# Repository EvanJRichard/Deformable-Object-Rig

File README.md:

Deformable-Object-Rig
=====================

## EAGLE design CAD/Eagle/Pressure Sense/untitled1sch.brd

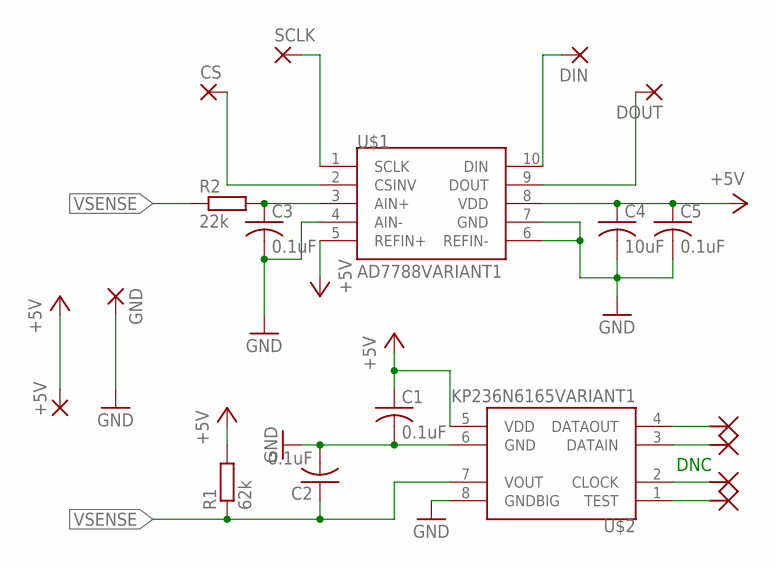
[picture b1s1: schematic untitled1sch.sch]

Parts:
+5V: WIREPAD1,6/0,8; 1,6/0,8
C1, C2, C3, C5: 0.1uF; C0805
C4: 10uF; C0805
CS: WIREPAD1,6/0,8; 1,6/0,8
DIN: WIREPAD1,6/0,8; 1,6/0,8
DOUT: WIREPAD1,6/0,8; 1,6/0,8
GND: WIREPAD1,6/0,8; 1,6/0,8
R1: 62k; R0603
R2: 22k; R0603
SCLK: WIREPAD1,6/0,8; 1,6/0,8
U$1: AD7788VARIANT1; AD7788
U$2: KP236N6165VARIANT1; KP236N6165

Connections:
+5V: +5V.1, C1.1, C4.1, C5.1, R1.2, U$1.5 (REFIN+), U$1.8 (VDD), U$2.5 (VDD)
GND: C1.2, C2.2, C3.2, C4.2, C5.2, GND.1, U$1.4 (AIN-), U$1.6 (REFIN-), U$1.7 (GND), U$2.6 (GND), U$2.8 (GNDBIG)
unnamed: CS.1, U$1.2 (CSINV)
unnamed: DIN.1, U$1.10 (DIN)
unnamed: DOUT.1, U$1.9 (DOUT)
RENAMED: C3.1, R2.2, U$1.3 (AIN+)
SCLK: SCLK.1, U$1.1 (SCLK)
VSENSE: C2.1, R1.1, R2.1, U$2.7 (VOUT)

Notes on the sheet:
DNC

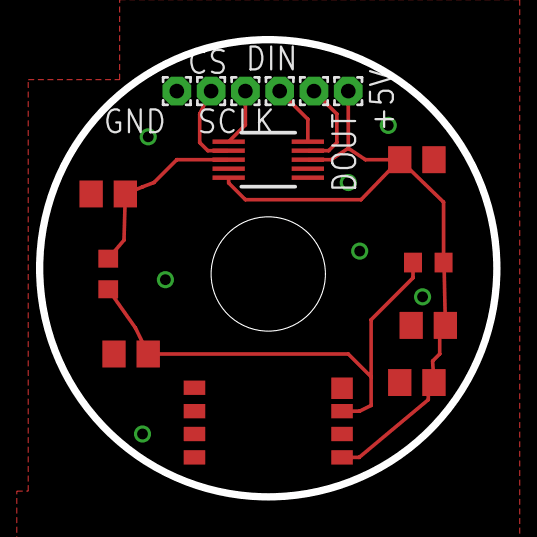
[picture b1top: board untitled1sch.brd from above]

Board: 2 copper layers, 25.4 x 25.4 mm, 15 parts (0 on the bottom side), 8 nets.

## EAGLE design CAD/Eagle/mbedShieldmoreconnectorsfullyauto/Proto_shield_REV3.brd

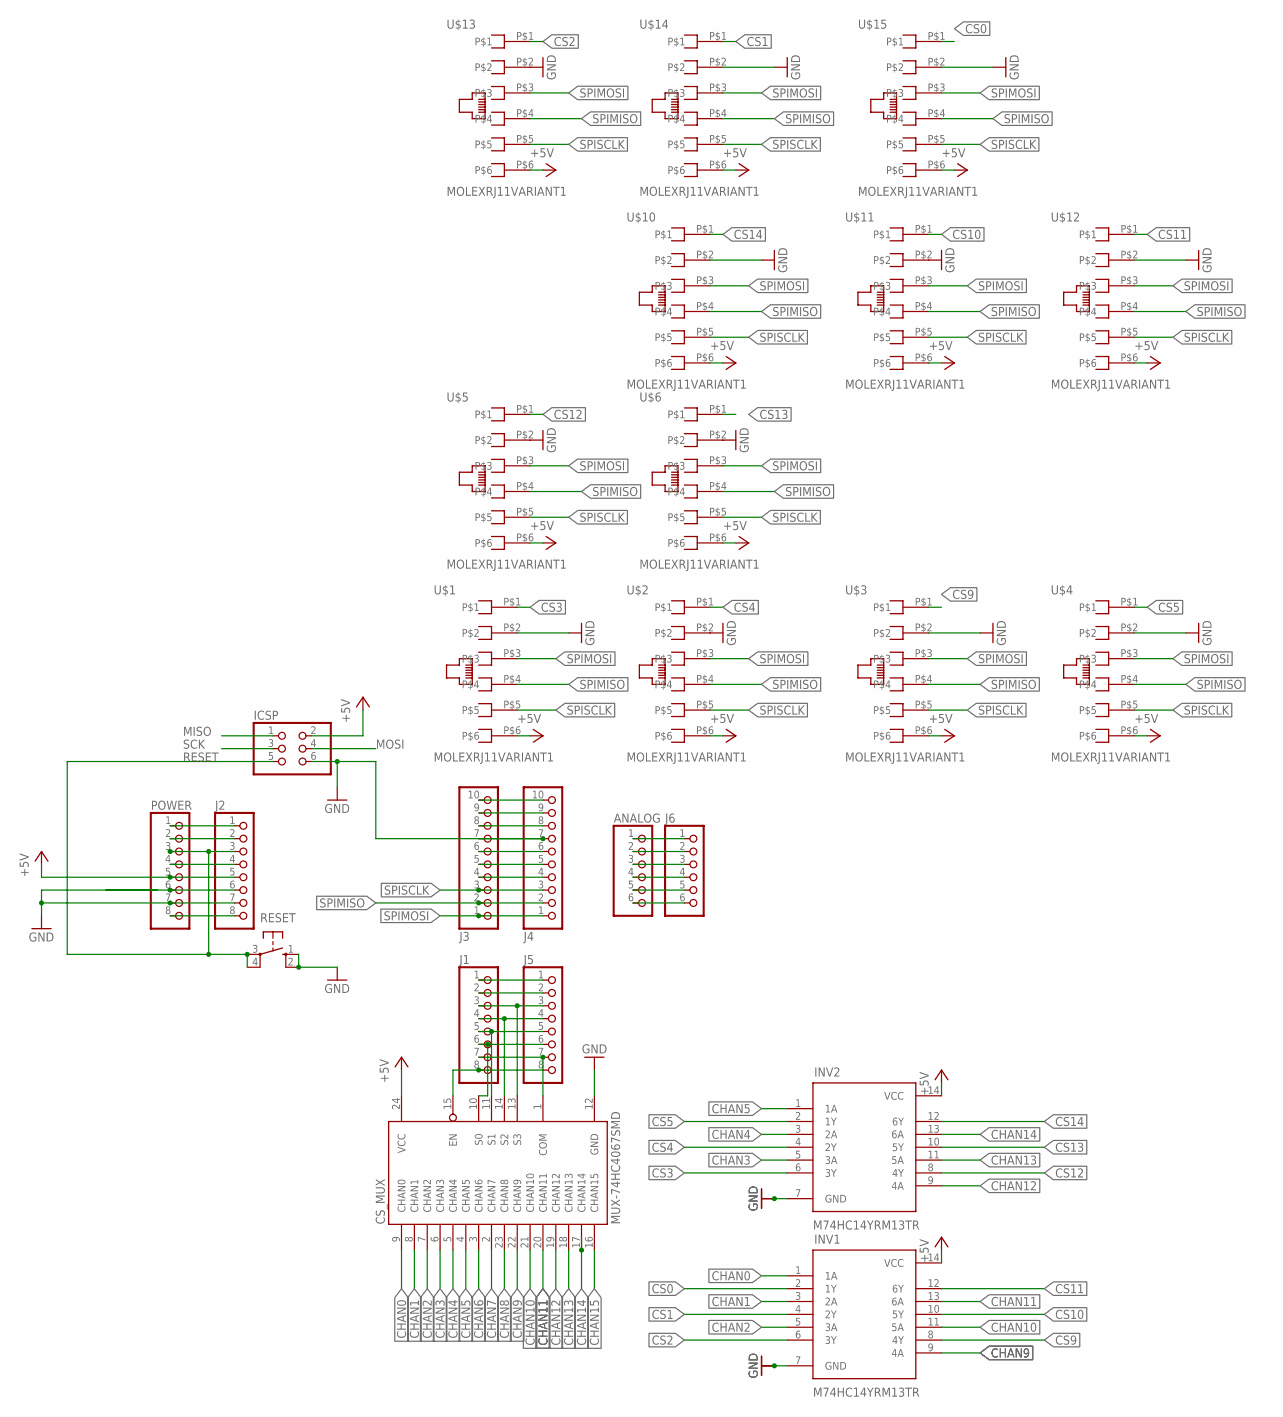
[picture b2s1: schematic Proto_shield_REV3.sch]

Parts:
ANALOG: PINHD-1X6; 1X06
CS_MUX: MUX-74HC4067SMD; SSOP24
ICSP: PINHD-2X3; 2X03
INV1, INV2: M74HC14YRM13TR; SO14
J1, J2, J5: PINHD-1X8TH; 1X08-TH
J3, J4: PINHD-1X10TH; 1X10-TH
J6: PINHD-1X6; 1X06
POWER: PINHD-1X8TH; 1X08-TH
RESET: 10-XX; B3F-10XX
U$1, U$2, U$3, U$4, U$5, U$6, U$10, U$11, U$12, U$13, U$14, U$15: MOLEXRJ11VARIANT1; RJ11MOLEX

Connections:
+5V: CS_MUX.24 (VCC), ICSP.2, INV1.14 (VCC), INV2.14 (VCC), J2.5, POWER.5, U$1.P$6, U$2.P$6, U$3.P$6, U$4.P$6, U$5.P$6, U$6.P$6, U$10.P$6, U$11.P$6, U$12.P$6, U$13.P$6, U$14.P$6, U$15.P$6
+9V: J2.8, POWER.8
CHAN0: CS_MUX.9 (CHAN0), INV1.1 (1A)
CHAN1: CS_MUX.8 (CHAN1), INV1.3 (2A)
CHAN2: CS_MUX.7 (CHAN2), INV1.5 (3A)
CHAN3: CS_MUX.6 (CHAN3), INV2.5 (3A)
CHAN4: CS_MUX.5 (CHAN4), INV2.3 (2A)
CHAN5: CS_MUX.4 (CHAN5), INV2.1 (1A)
CHAN6: CS_MUX.3 (CHAN6)
CHAN7: CS_MUX.2 (CHAN7)
CHAN8: CS_MUX.23 (CHAN8)
CHAN9: CS_MUX.22 (CHAN9), INV1.9 (4A)
CHAN10: CS_MUX.21 (CHAN10), INV1.11 (5A)
CHAN11: CS_MUX.20 (CHAN11), INV1.13 (6A)
CHAN12: CS_MUX.19 (CHAN12), INV2.9 (4A)
CHAN13: CS_MUX.18 (CHAN13), INV2.11 (5A)
CHAN14: CS_MUX.17 (CHAN14), INV2.13 (6A)
CHAN15: CS_MUX.16 (CHAN15)
CS0: INV1.2 (1Y), U$15.P$1
CS1: INV1.4 (2Y), U$14.P$1
CS2: INV1.6 (3Y), U$13.P$1
CS3: INV2.6 (3Y), U$1.P$1
CS4: INV2.4 (2Y), U$2.P$1
CS5: INV2.2 (1Y), U$4.P$1
CS9: INV1.8 (4Y), U$3.P$1
CS10: INV1.10 (5Y), U$11.P$1
CS11: INV1.12 (6Y), U$12.P$1
CS12: INV2.8 (4Y), U$5.P$1
CS13: INV2.10 (5Y), U$6.P$1
CS14: INV2.12 (6Y), U$10.P$1
GND: CS_MUX.12 (GND), ICSP.6, INV1.7 (GND), INV2.7 (GND), J2.7, J3.7, J4.7, POWER.7, RESET.1 (S), RESET.2 (S1), U$1.P$2, U$2.P$2, U$3.P$2, U$4.P$2, U$5.P$2, U$6.P$2, U$10.P$2, U$11.P$2, U$12.P$2, U$13.P$2, U$14.P$2, U$15.P$2
MISO: ICSP.1
MOSI: ICSP.4
unnamed: J3.6, J4.6
unnamed: J3.4, J4.4
unnamed: J3.5, J4.5
unnamed: J1.1, J5.1
unnamed: J1.2, J5.2
unnamed: CS_MUX.13 (S3), J1.3, J5.3
unnamed: CS_MUX.14 (S2), J1.4, J5.4
unnamed: CS_MUX.11 (S1), J1.5, J5.5
unnamed: CS_MUX.10 (S0), J1.6, J5.6
unnamed: CS_MUX.1 (COM), J1.7, J5.7
unnamed: CS_MUX.15 (EN), J1.8, J5.8
unnamed: ANALOG.1, J6.1
unnamed: ANALOG.2, J6.2
unnamed: ANALOG.3, J6.3
unnamed: ANALOG.4, J6.4
unnamed: ANALOG.5, J6.5
unnamed: ANALOG.6, J6.6
unnamed: J2.6, POWER.6
unnamed: J2.2, POWER.2
unnamed: J2.1, POWER.1
unnamed: J3.9, J4.9
unnamed: J3.10, J4.10
unnamed: J3.8, J4.8
unnamed: J2.4, POWER.4
RESET: ICSP.5, J2.3, POWER.3, RESET.3, RESET.4 (P1)
SCK: ICSP.3
SPIMISO: J3.2, J4.2, U$1.P$4, U$2.P$4, U$3.P$4, U$4.P$4, U$5.P$4, U$6.P$4, U$10.P$4, U$11.P$4, U$12.P$4, U$13.P$4, U$14.P$4, U$15.P$4
SPIMOSI: J3.1, J4.1, U$1.P$3, U$2.P$3, U$3.P$3, U$4.P$3, U$5.P$3, U$6.P$3, U$10.P$3, U$11.P$3, U$12.P$3, U$13.P$3, U$14.P$3, U$15.P$3
SPISCLK: J3.3, J4.3, U$1.P$5, U$2.P$5, U$3.P$5, U$4.P$5, U$5.P$5, U$6.P$5, U$10.P$5, U$11.P$5, U$12.P$5, U$13.P$5, U$14.P$5, U$15.P$5

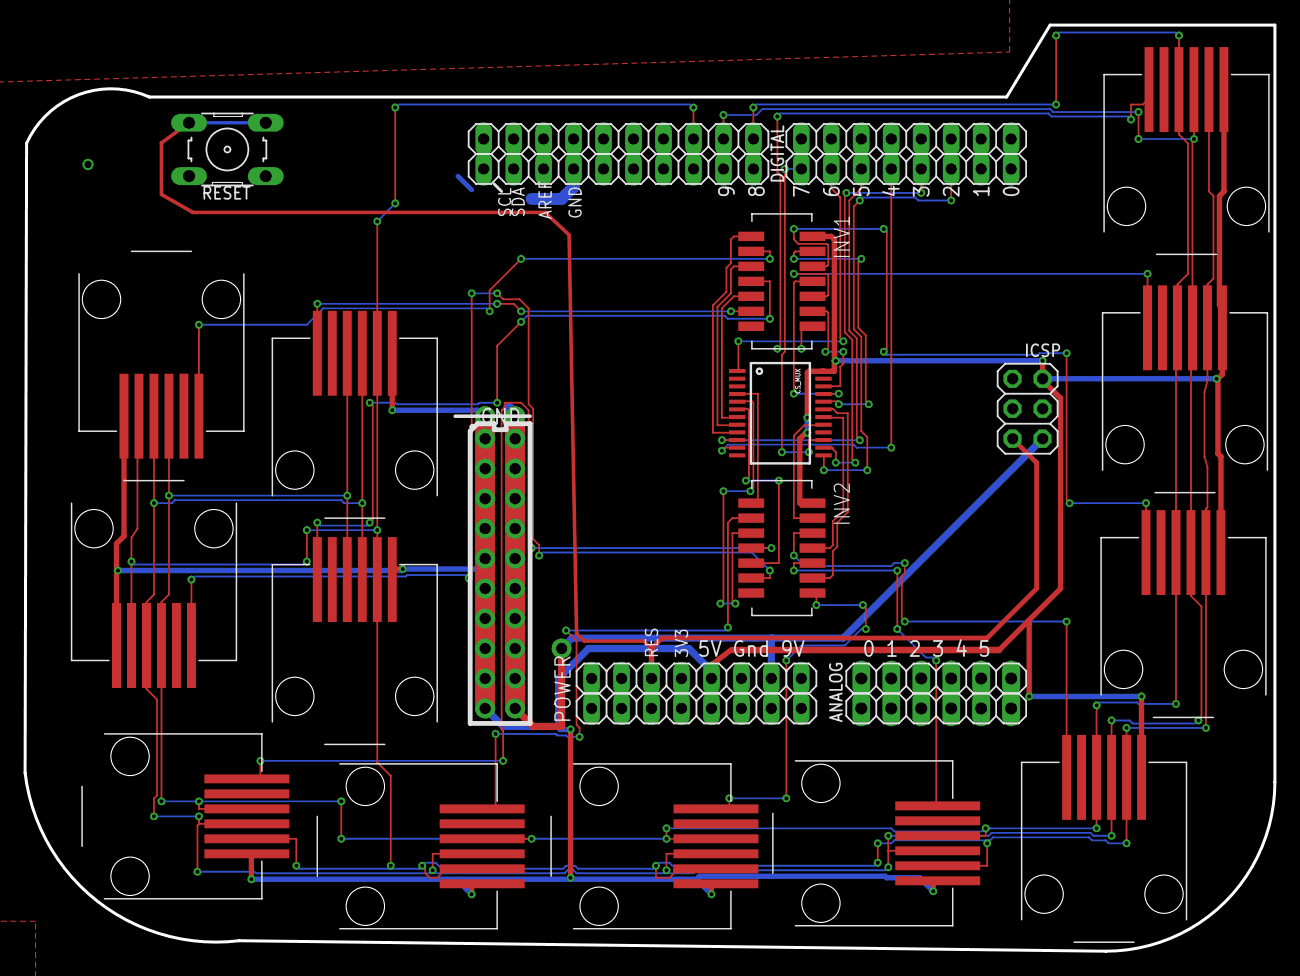
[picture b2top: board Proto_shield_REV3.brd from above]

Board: 2 copper layers, 105.9 x 78.5 mm, 25 parts (0 on the bottom side), 55 nets.

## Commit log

2014-08-22 all files
    Final commit for WPI ARC Lab Deformable Object Testbed project.
2014-08-22 commenting
2015-02-27 Switch from ADC to ATTiny
